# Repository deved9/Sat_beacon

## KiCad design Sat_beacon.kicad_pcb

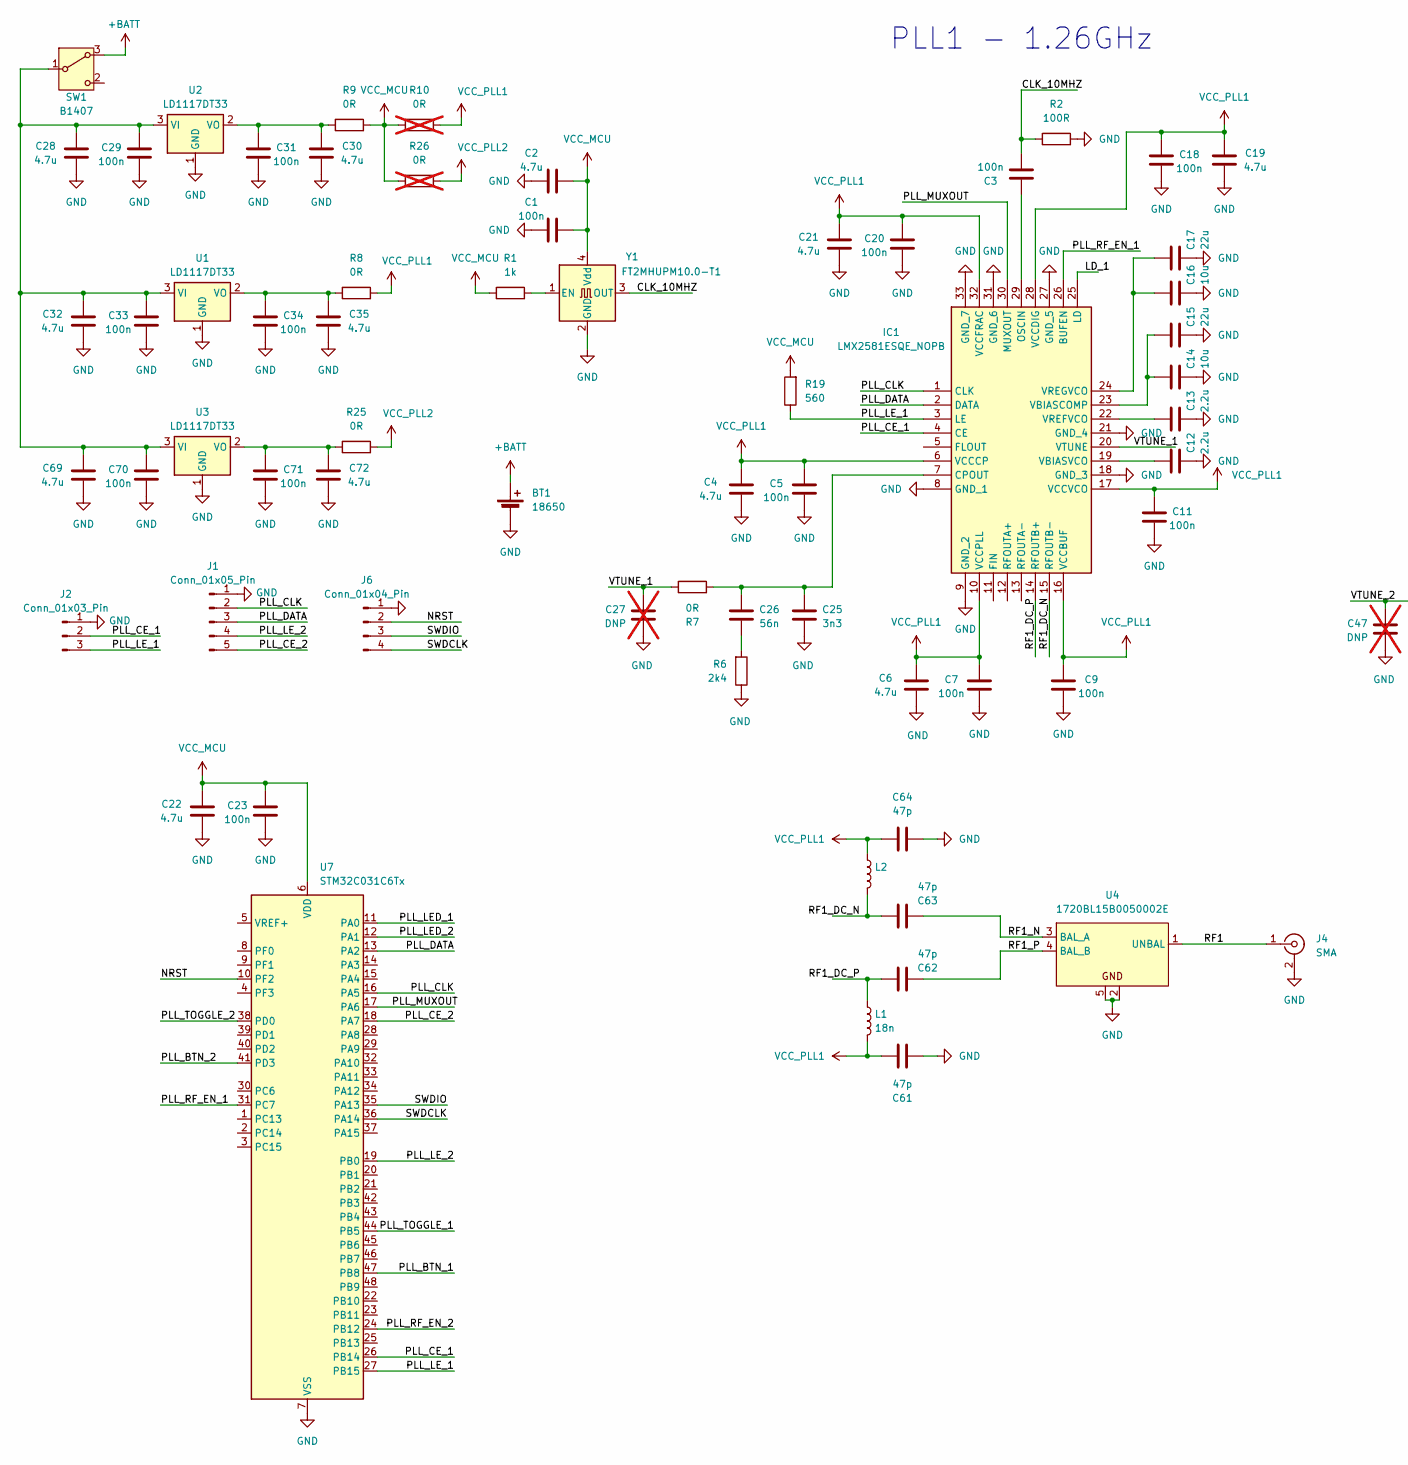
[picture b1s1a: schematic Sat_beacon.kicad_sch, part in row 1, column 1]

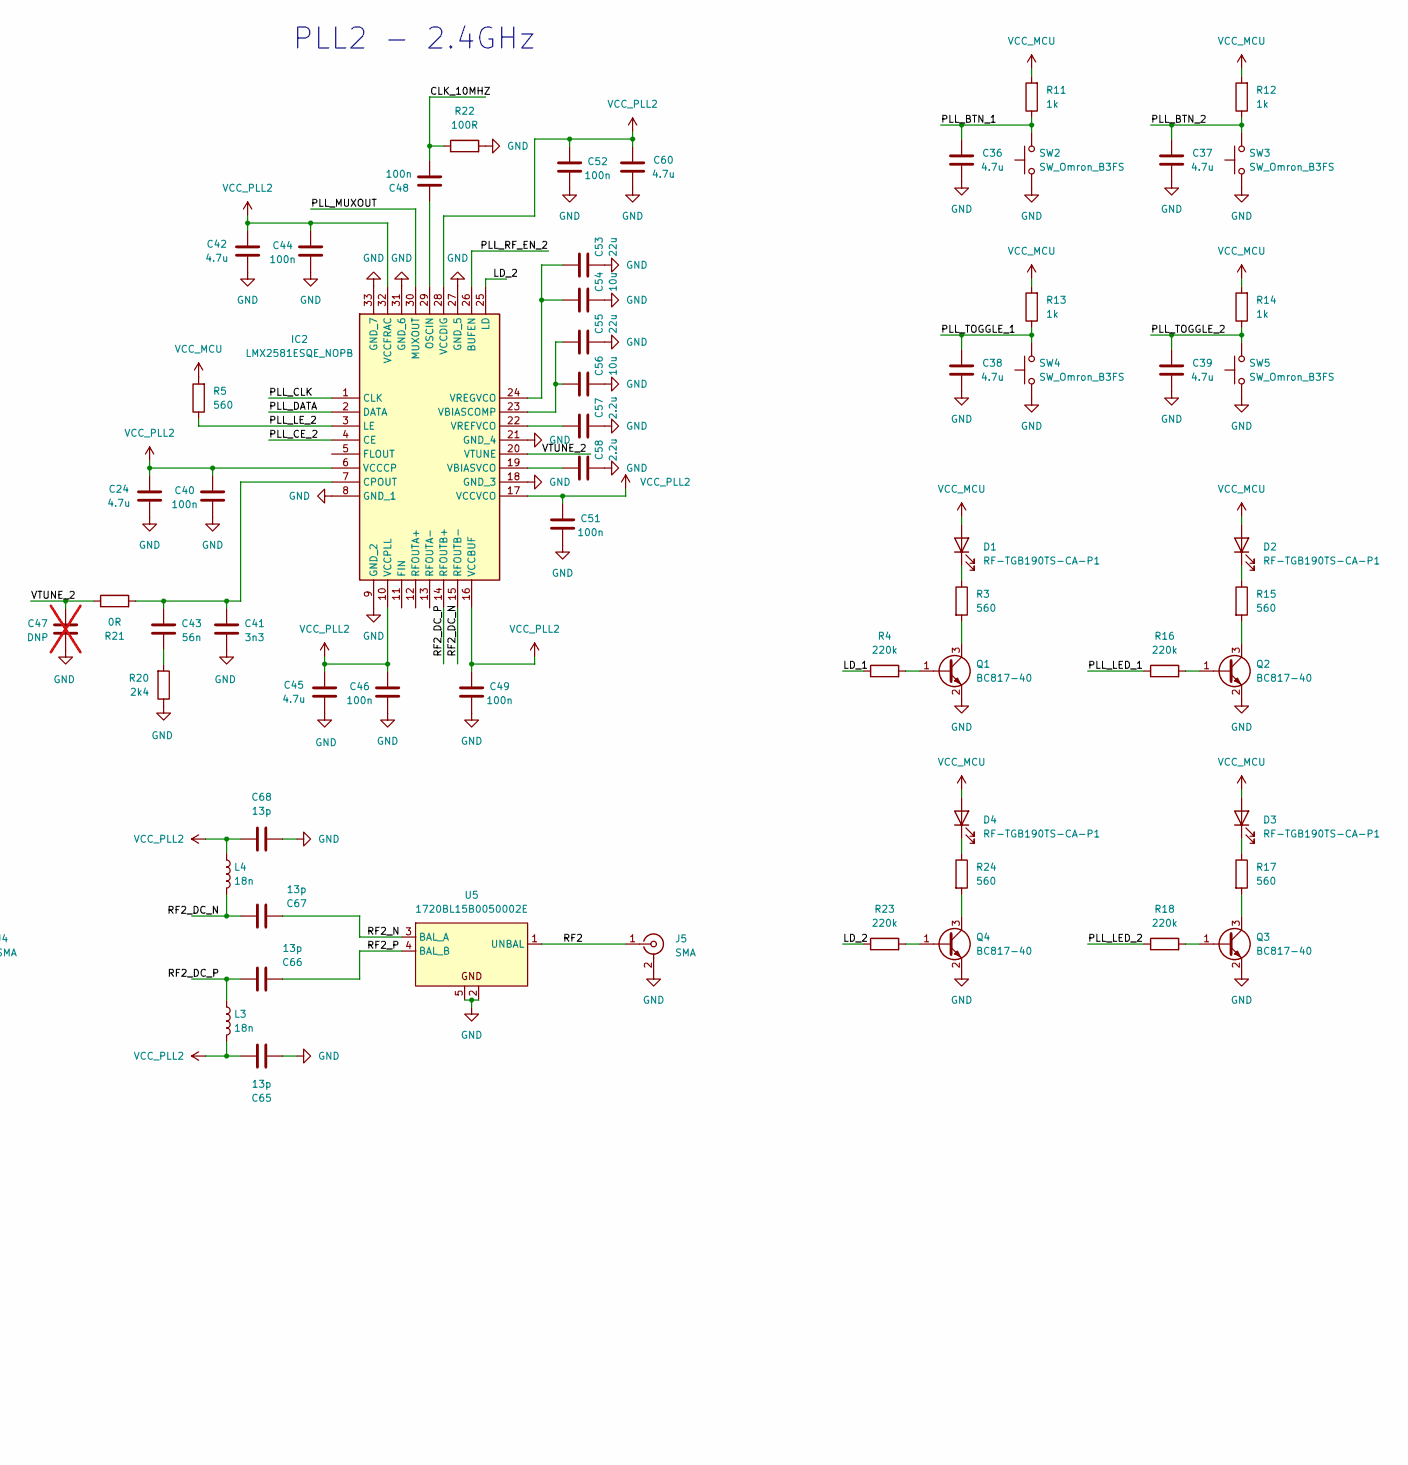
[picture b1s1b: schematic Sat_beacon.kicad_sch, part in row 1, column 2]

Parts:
BT1: 18650; BatteryHolder_MPD_BH-18650-PC
C1, C3, C5, C7, C9, C11, C18, C20, C23, C29, C31, C33, C34, C40, C44, C46, C48, C49, C51, C52, C70, C71: 100n; C_0603_1608Metric
C2, C4, C6, C19, C21, C22, C24, C28, C30, C32, C35, C36, C37, C38, C39, C42, C45, C60, C69, C72: 4.7u; C_0805_2012Metric
C12, C13, C57, C58: 2.2u; C_0603_1608Metric
C14, C16, C54, C56: 10u; C_0603_1608Metric
C15, C17, C53, C55: 22u; C_0805_2012Metric
C25, C41: 3n3; C_0603_1608Metric
C26, C43: 56n; C_0603_1608Metric
C27, C47: DNP; C_0603_1608Metric; not fitted
C61, C62, C63, C64: 47p; C_0402_1005Metric
C65, C66, C67, C68: 13p; C_0402_1005Metric
D1, D2, D3, D4: RF-TGB190TS-CA-P1; LED_0603_1608Metric
IC1, IC2: LMX2581ESQE_NOPB; QFN50P500X500X80-33M; Mouser Part Number 595-LMX2581ESQE/NOPB
J1: Conn_01x05_Pin; PinHeader_1x05_P2.54mm_Vertical
J2: Conn_01x03_Pin; PinHeader_1x03_P2.54mm_Vertical
J4, J5: SMA; SMA_Amphenol_132289_EdgeMount
J6: Conn_01x04_Pin; PinHeader_1x04_P2.54mm_Vertical
L1, L2, L3, L4: 18n; L_0603_1608Metric
Q1, Q2, Q3, Q4: BC817-40; SOT-23
R1, R11, R12, R13, R14: 1k; R_0603_1608Metric
R2, R22: 100R; R_0805_2012Metric
R3, R15, R17, R24: 560; R_1206_3216Metric
R4, R16, R18, R23: 220k; R_0603_1608Metric
R5, R19: 560; R_0603_1608Metric
R6, R20: 2k4; R_0603_1608Metric
R7, R8, R9, R21, R25: 0R; R_0603_1608Metric
R10, R26: 0R; R_0603_1608Metric; not fitted
SW1: B1407; flip_switch
SW2, SW3, SW4, SW5: SW_Omron_B3FS; SW_SPST_Omron_B3FS-105xP
U1, U2, U3: LD1117DT33; TO-252-3_TabPin2
U4, U5: 1720BL15B0050002E; Balun_Johanson_0896BM15A0001
U7: STM32C031C6Tx; LQFP-48_7x7mm_P0.5mm
Y1: FT2MHUPM10.0-T1; Oscillator_SMD_SiT_PQFN-4Pin_2.5x2.0mm

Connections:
+BATT: BT1.1 (+), SW1.3 (A)
/CLK_10MHZ: C3.2, C48.2, R2.1, R22.1, Y1.3 (OUT)
/LD_1: IC1.25 (LD), R4.1
/LD_2: IC2.25 (LD), R23.1
/NRST: J6.2, U7.10 (PF2)
/PLL_BTN_1: C36.2, R11.1, SW2.2, U7.47 (PB8)
/PLL_BTN_2: C37.2, R12.1, SW3.2, U7.41 (PD3)
/PLL_CE_1: IC1.4 (CE), J2.2, U7.26 (PB14)
/PLL_CE_2: IC2.4 (CE), J1.5, U7.18 (PA7)
/PLL_CLK: IC1.1 (CLK), IC2.1 (CLK), J1.2, U7.16 (PA5)
/PLL_DATA: IC1.2 (DATA), IC2.2 (DATA), J1.3, U7.13 (PA2)
/PLL_LED_1: R16.1, U7.11 (PA0)
/PLL_LED_2: R18.1, U7.12 (PA1)
/PLL_LE_1: IC1.3 (LE), J2.3, R19.1, U7.27 (PB15)
/PLL_LE_2: IC2.3 (LE), J1.4, R5.1, U7.19 (PB0)
/PLL_RF_EN_1: IC1.26 (BUFEN), U7.31 (PC7)
/PLL_RF_EN_2: IC2.26 (BUFEN), U7.24 (PB12)
/PLL_TOGGLE_1: C38.2, R13.1, SW4.2, U7.44 (PB5)
/PLL_TOGGLE_2: C39.2, R14.1, SW5.2, U7.38 (PD0)
/RF1: J4.1 (In), U4.1 (UNBAL)
/RF1_DC_N: C63.1, IC1.15 (RFOUTB-), L2.2
/RF1_DC_P: C62.1, IC1.14 (RFOUTB+), L1.1
/RF1_N: C63.2, U4.3 (BAL_A)
/RF1_P: C62.2, U4.4 (BAL_B)
/RF2: J5.1 (In), U5.1 (UNBAL)
/RF2_DC_N: C67.1, IC2.15 (RFOUTB-), L4.2
/RF2_DC_P: C66.1, IC2.14 (RFOUTB+), L3.1
/RF2_N: C67.2, U5.3 (BAL_A)
/RF2_P: C66.2, U5.4 (BAL_B)
/SWDCLK: J6.4, U7.36 (PA14)
/SWDIO: J6.3, U7.35 (PA13)
/VTUNE_1: C27.2, IC1.20 (VTUNE), R7.1
/VTUNE_2: C47.2, IC2.20 (VTUNE), R21.1
GND: BT1.2 (-), C1.1, C2.1, C4.1, C5.1, C6.1, C7.1, C9.1, C11.1, C12.1, C13.1, C14.1, C15.1, C16.1, C17.1, C18.1, C19.1, C20.1, C21.1, C22.1, C23.1, C24.1, C25.1, C27.1, C28.1, C29.1, C30.1, C31.1, C32.1, C33.1, C34.1, C35.1, C36.1, C37.1, C38.1, C39.1, C40.1, C41.1, C42.1, C44.1, C45.1, C46.1, C47.1, C49.1, C51.1, C52.1, C53.1, C54.1, C55.1, C56.1, C57.1, C58.1, C60.1, C61.2, C64.2, C65.2, C68.2, C69.1, C70.1, C71.1, C72.1, IC1.8 (GND_1), IC1.9 (GND_2), IC1.18 (GND_3), IC1.21 (GND_4), IC1.27 (GND_5), IC1.31 (GND_6), IC1.33 (GND_7), IC2.8 (GND_1), IC2.9 (GND_2), IC2.18 (GND_3), IC2.21 (GND_4), IC2.27 (GND_5), IC2.31 (GND_6), IC2.33 (GND_7), J1.1, J2.1, J4.2 (Ext), J5.2 (Ext), J6.1, Q1.2 (E), Q2.2 (E), Q3.2 (E), Q4.2 (E), R2.2, R6.1, R20.1, R22.2, SW2.1, SW3.1, SW4.1, SW5.1, U1.1 (GND), U2.1 (GND), U3.1 (GND), U4.2, U4.5, U5.2, U5.5, U7.7 (VSS), Y1.2 (GND)
unnamed: C26.1, R6.2
unnamed: C43.1, R20.2
unnamed: D1.1 (K), R3.1
unnamed: D2.1 (K), R15.1
unnamed: D3.1 (K), R17.1
unnamed: D4.1 (K), R24.1
unnamed: C25.2, C26.2, IC1.7 (CPOUT), R7.2
unnamed: C3.1, IC1.29 (OSCIN)
unnamed: C14.2, C15.2, IC1.23 (VBIASCOMP)
unnamed: C12.2, IC1.19 (VBIASVCO)
unnamed: C13.2, IC1.22 (VREFVCO)
unnamed: C16.2, C17.2, IC1.24 (VREGVCO)
unnamed: C41.2, C43.2, IC2.7 (CPOUT), R21.2
unnamed: C48.1, IC2.29 (OSCIN)
unnamed: C55.2, C56.2, IC2.23 (VBIASCOMP)
unnamed: C58.2, IC2.19 (VBIASVCO)
unnamed: C57.2, IC2.22 (VREFVCO)
unnamed: C53.2, C54.2, IC2.24 (VREGVCO)
unnamed: Q1.1 (B), R4.2
unnamed: Q1.3 (C), R3.2
unnamed: Q2.1 (B), R16.2
unnamed: Q2.3 (C), R15.2
unnamed: Q3.1 (B), R18.2
unnamed: Q3.3 (C), R17.2
unnamed: Q4.1 (B), R23.2
unnamed: Q4.3 (C), R24.2
unnamed: C28.2, C29.2, C32.2, C33.2, C69.2, C70.2, SW1.1 (B), U1.3 (VI), U2.3 (VI), U3.3 (VI)
unnamed: C34.2, C35.2, R8.2, U1.2 (VO)
unnamed: C30.2, C31.2, R9.2, U2.2 (VO)
unnamed: C71.2, C72.2, R25.2, U3.2 (VO)
unnamed: R1.2, Y1.1 (EN)
VCC_MCU: C1.2, C2.2, C22.2, C23.2, D1.2 (A), D2.2 (A), D3.2 (A), D4.2 (A), R1.1, R5.2, R9.1, R10.2, R11.2, R12.2, R13.2, R14.2, R19.2, R26.2, U7.6 (VDD), Y1.4 (Vdd)
VCC_PLL1: C4.2, C5.2, C6.2, C7.2, C9.2, C11.2, C18.2, C19.2, C20.2, C21.2, C61.1, C64.1, IC1.6 (VCCCP), IC1.10 (VCCPLL), IC1.16 (VCCBUF), IC1.17 (VCCVCO), IC1.28 (VCCDIG), IC1.32 (VCCFRAC), L1.2, L2.1, R8.1, R10.1
VCC_PLL2: C24.2, C40.2, C42.2, C44.2, C45.2, C46.2, C49.2, C51.2, C52.2, C60.2, C65.1, C68.1, IC2.6 (VCCCP), IC2.10 (VCCPLL), IC2.16 (VCCBUF), IC2.17 (VCCVCO), IC2.28 (VCCDIG), IC2.32 (VCCFRAC), L3.2, L4.1, R25.1, R26.1

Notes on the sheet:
PLL2 - 2.4GHz
PLL1 - 1.26GHz

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
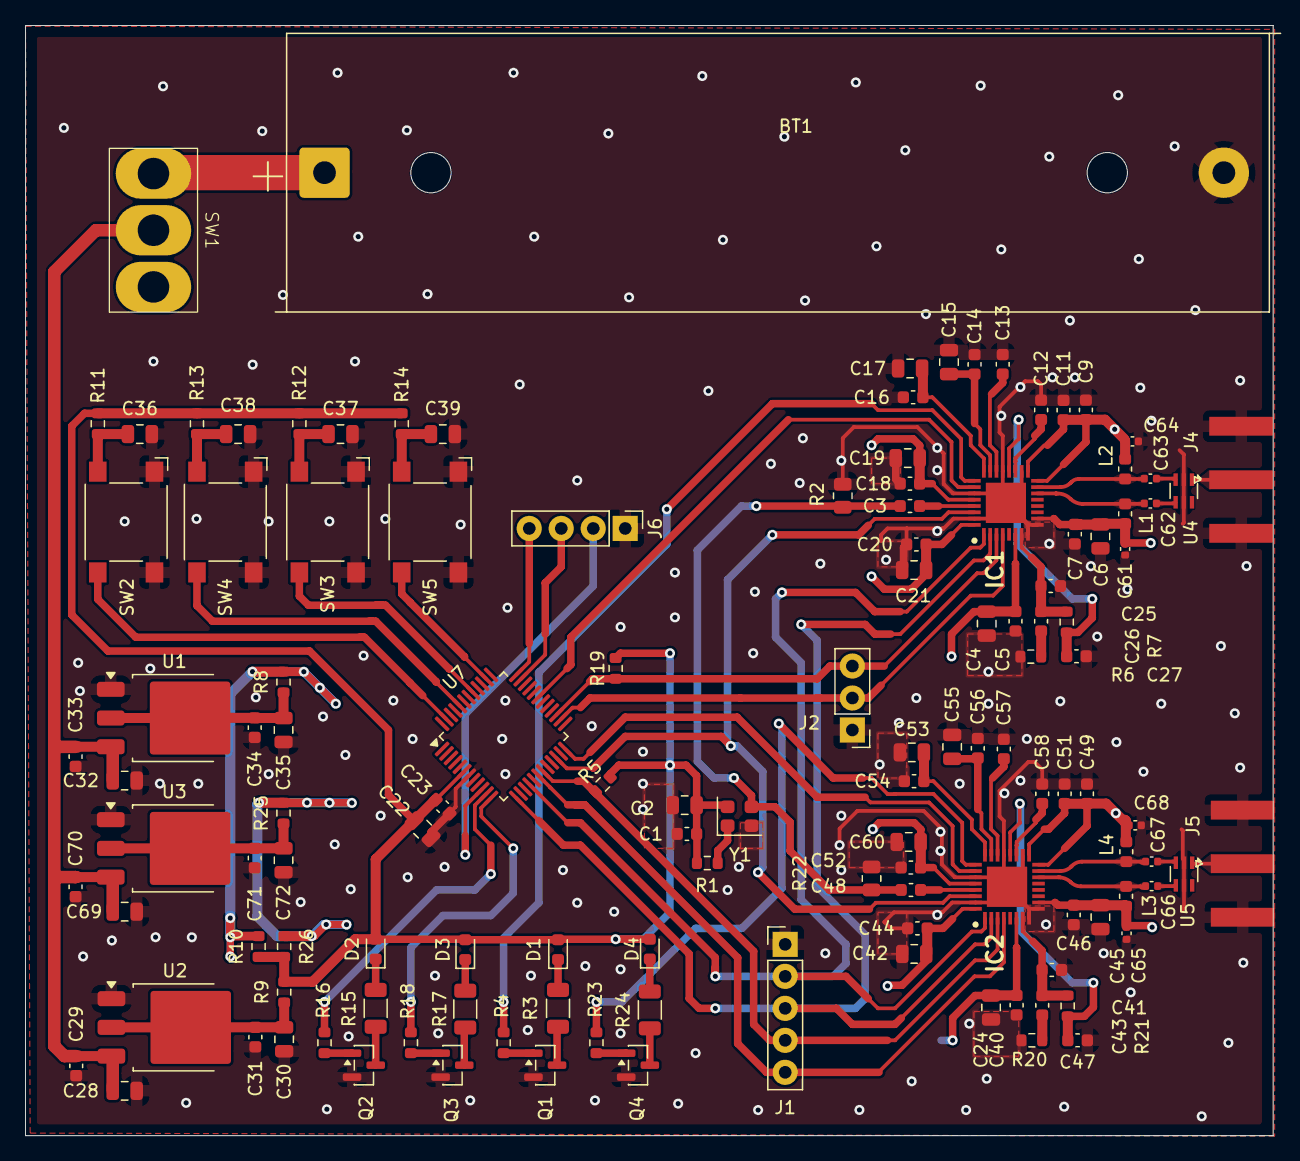
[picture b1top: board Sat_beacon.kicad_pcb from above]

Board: 4 copper layers, 99.1 x 88.1 mm, 126 parts (0 on the bottom side), 69 nets.

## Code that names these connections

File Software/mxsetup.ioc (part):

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Mcu.Name=STM32C031C(4-6)Tx
Mcu.Package=LQFP48
Mcu.UserName=STM32C031C6Tx
PA0.GPIOParameters=GPIO_Label
PA0.GPIO_Label=PLL_LED_1
PA0.Signal=GPIO_Output
PA1.GPIOParameters=GPIO_Label
PA1.GPIO_Label=PLL_LED_2
PA1.Signal=GPIO_Output
PA11\ [PA9].GPIOParameters=GPIO_Label,GPIO_Speed
PA11\ [PA9].GPIO_Label=PLL_MUXout
PA11\ [PA9].GPIO_Speed=GPIO_SPEED_FREQ_VERY_HIGH
PA11\ [PA9].Mode=Full_Duplex_Master
PA11\ [PA9].Signal=SPI1_MISO
PA13.Mode=Serial_Wire
PA13.Signal=DEBUG_SWDIO
PA14-BOOT0.Mode=Serial_Wire
PA14-BOOT0.Signal=DEBUG_SWCLK
PA2.GPIOParameters=GPIO_Speed,GPIO_Label
PA2.GPIO_Label=PLL_DATA
PA2.GPIO_Speed=GPIO_SPEED_FREQ_VERY_HIGH
PA2.Mode=Full_Duplex_Master
PA2.Signal=SPI1_MOSI
PA5.GPIOParameters=GPIO_Speed,GPIO_Label
PA5.GPIO_Label=PLL_CLK
PA5.GPIO_Speed=GPIO_SPEED_FREQ_VERY_HIGH
PA5.Mode=Full_Duplex_Master
PA5.Signal=SPI1_SCK
PA7.GPIOParameters=GPIO_Label
PA7.GPIO_Label=PLL_CE_2
PA7.Signal=GPIO_Output
PB0.GPIOParameters=PinState,GPIO_PuPd,GPIO_Label,GPIO_ModeDefaultOutputPP
PB0.GPIO_Label=PLL_LE_2
PB0.GPIO_ModeDefaultOutputPP=GPIO_MODE_OUTPUT_PP
PB0.GPIO_PuPd=GPIO_NOPULL
PB0.PinState=GPIO_PIN_RESET
PB0.Signal=GPIO_Output
PB12.GPIOParameters=GPIO_Label
PB12.GPIO_Label=PLL_RF_EN_2
PB12.Signal=GPIO_Output
PB14.GPIOParameters=GPIO_Label
PB14.GPIO_Label=PLL_CE_1
PB14.Signal=GPIO_Output
PB15.GPIOParameters=PinState,GPIO_PuPd,GPIO_Label,GPIO_ModeDefaultOutputPP
PB15.GPIO_Label=PLL_LE_1
PB15.GPIO_ModeDefaultOutputPP=GPIO_MODE_OUTPUT_PP
PB15.GPIO_PuPd=GPIO_NOPULL
PB15.PinState=GPIO_PIN_RESET
PB15.Signal=GPIO_Output
PB5.GPIOParameters=GPIO_Label
PB5.GPIO_Label=PLL_TOGGLE_1
PB5.Signal=GPIO_Input
PB8.GPIOParameters=GPIO_PuPd,GPIO_Label
PB8.GPIO_Label=PLL_BTN_1
PB8.GPIO_PuPd=GPIO_NOPULL
PB8.Signal=GPIO_Input
PC7.GPIOParameters=GPIO_Label
PC7.GPIO_Label=PLL_RF_EN_1
PC7.Signal=GPIO_Output
PD0.GPIOParameters=GPIO_PuPd,GPIO_Label
PD0.GPIO_Label=PLL_TOGGLE_2
PD0.GPIO_PuPd=GPIO_NOPULL
PD0.Signal=GPIO_Input
PD3.GPIOParameters=GPIO_PuPd,GPIO_Label
PD3.GPIO_Label=PLL_BTN_2
PD3.GPIO_PuPd=GPIO_NOPULL
PD3.Signal=GPIO_Input
RCC.HSE_VALUE=8000000
RCC.SYSCLKFreq_VALUE=48000000
board=custom

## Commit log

2026-02-25 added pin headers + signal nets fixes
2026-02-26 MCU-to-PLL pins added. Software folder created
2026-02-26 picked LEDs and fixed resistors
2026-02-27 PLL_LE pullup added
2026-02-27 fixed PLL caps
2026-02-27 RF balun added
2026-03-01 PLL RF enable added
2026-03-01 Fixed VTUNE, added battery, power switch, RF caps, net labels
2026-03-02 RF C added, replacement needed
2026-03-02 footprint fixes, BOM and CSV generated
2026-03-02 Separated PLL power
2026-03-02 MMCX model added
2026-03-03 MCU swap, IOC created
2026-03-03 Group and place components on PCB, two PLL caps removed, swapped RF lines
2026-03-03 SW: LMX2581 registers mapped
2026-03-06 PCB work
2026-03-09 MUXout added, LEDs swapped (SCH only)
2026-03-11 NRST pin added
2026-03-12 PCB stackup and rules defined, some PCB work done
2026-03-20 SW: Switched to SPI
2026-03-21 PCB work + MCU pin moves
2026-03-23 PCB routed
2026-03-24 PCB RF section improvement
2026-03-25 new branch for 4 layer board, PCB updated, MMCX -> SMA
2026-03-26 PCB improvements
2026-03-26 PCB constrains updated for china + added vias, improved vias thanks to improved constrains
2026-03-27 PCB done and ordered
2026-04-08 [SW] LL_SPI done
2026-04-28 PLL not responding
2026-04-28 fix schematic
2026-04-29 SW done
2026-05-11 Modifications made while making it run + PLL filter design
